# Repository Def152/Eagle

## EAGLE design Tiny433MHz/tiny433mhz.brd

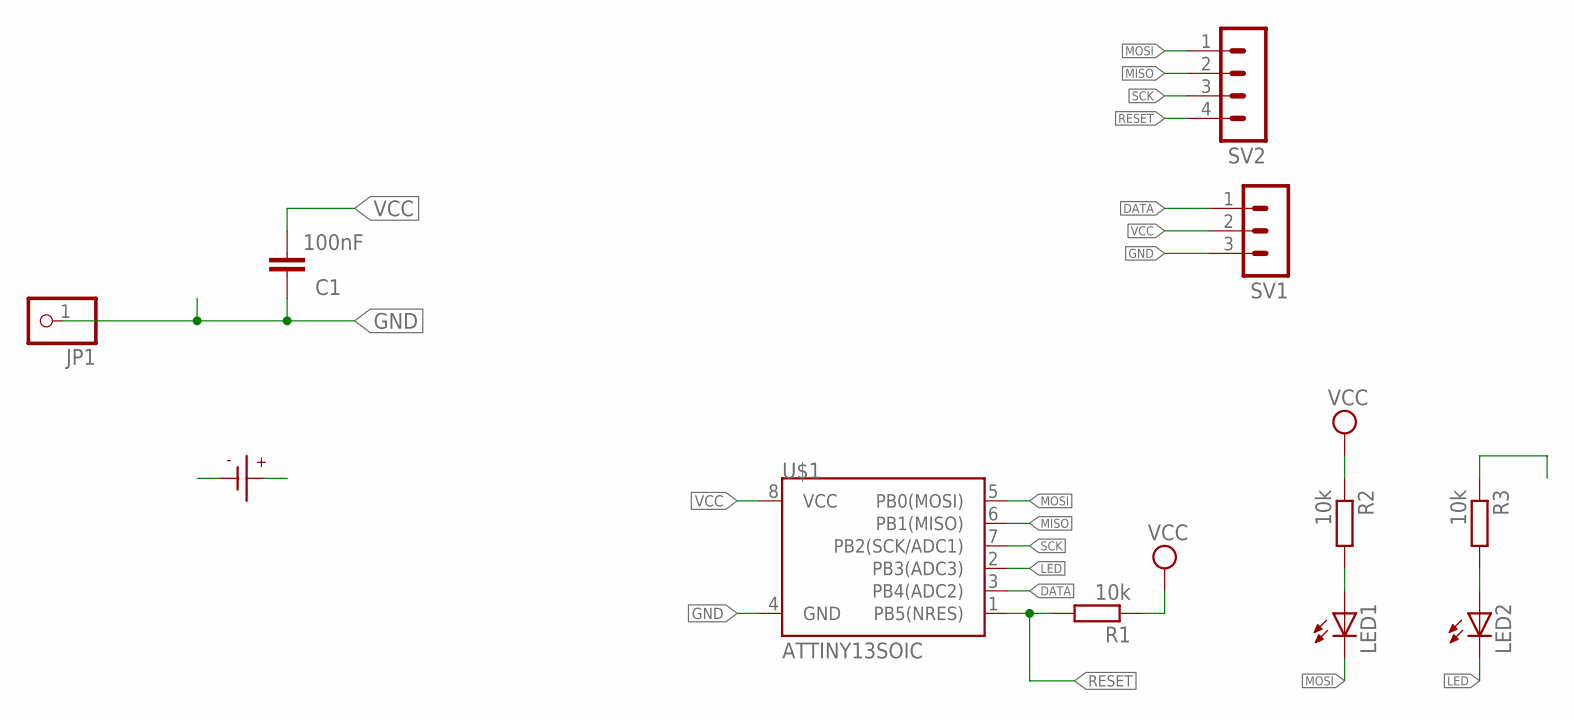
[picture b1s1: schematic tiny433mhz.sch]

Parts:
C1: 100nF; C0805
JP1: PINHD-1X1; 1X01
LED1, LED2: LEDCHIP-LED0805; CHIP-LED0805
R1, R2, R3: 10k; R0805
SV1: MA03-1
SV2: MA04-1
U$1: ATTINY13SOIC; SO08
U$3: CR2032; CR2032-THT

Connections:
DATA: SV1.1, U$1.3 (PB4(ADC2))
GND: C1.1, JP1.1, R3.1, SV1.3, U$1.4 (GND), U$3.-
LED: LED2.C, U$1.2 (PB3(ADC3))
MISO: SV2.2, U$1.6 (PB1(MISO))
MOSI: LED1.C, SV2.1, U$1.5 (PB0(MOSI))
unnamed: LED2.A, R3.2
unnamed: LED1.A, R2.2
RESET: R1.2, SV2.4, U$1.1 (PB5(NRES))
SCK: SV2.3, U$1.7 (PB2(SCK/ADC1))
VCC: C1.2, R1.1, R2.1, SV1.2, U$1.8 (VCC), U$3.+

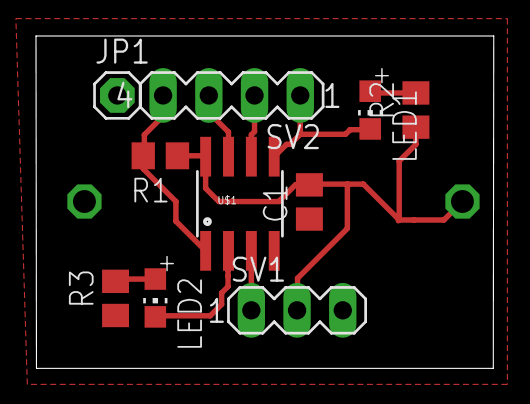
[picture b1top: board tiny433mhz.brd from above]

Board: 2 copper layers, 25.4 x 18.5 mm, 11 parts (1 on the bottom side), 10 nets.

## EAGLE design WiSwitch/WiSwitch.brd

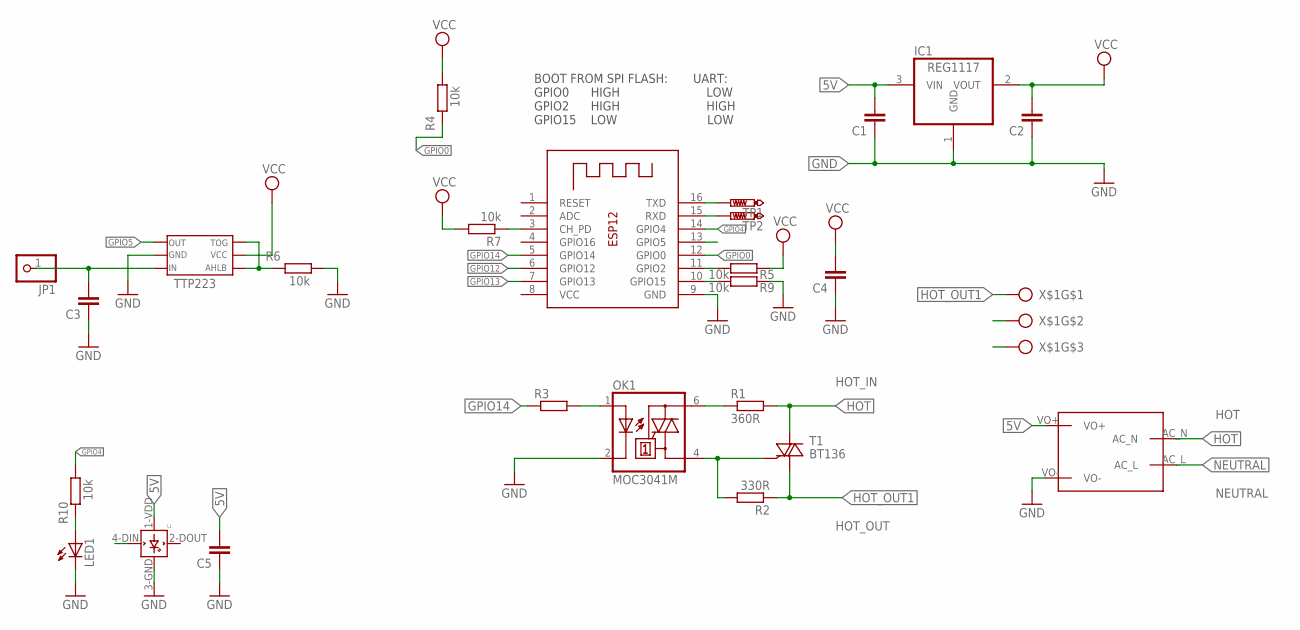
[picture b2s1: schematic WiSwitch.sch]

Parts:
C1, C2, C3, C4, C5: C-EUC0805; C0805
IC1: REG1117; SOT223
JP1: PINHD-1X1; 1X01
L1: WS2812B
LED1: LEDCHIP-LED0805; CHIP-LED0805
OK1: MOC3041M; DIL06
R1: 360R; 0207/10
R2: 330R; 0207/10
R3: R-EU_R0805; R0805
R4, R5, R6, R9, R10: 10k; R0805
R7: 10k; R0603
T1: BT136; TO220AB
TP1, TP2: PTR1B1,27; B1,27
U$2: MAINS_CONVERTERS; HLK-PM01
U$3: TTP223-BA6; SOT-23-6L
X1: ESP-12
X$1: ARK3

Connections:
5V: C1.2, C5.2, IC1.3 (VIN), L1.1-VDD (VDD), U$2.VO+
GND: C1.1, C2.1, C3.1, C4.1, C5.1, IC1.1 (GND), L1.3-GND (GND), LED1.C, OK1.2 (C), R6.2, R9.2, U$2.VO-, U$3.GND, X1.9 (GND)
GPIO0: R4.1, X1.12 (GPIO0)
GPIO4: R10.2, X1.14 (GPIO4)
GPIO5: U$3.OUT, X1.13 (GPIO5)
GPIO12: X1.6 (GPIO12)
GPIO13: L1.4-DIN (DIN), X1.7 (GPIO13)
GPIO14: R3.1, X1.5 (GPIO14)
HOT: R1.2, T1.2 (A2), U$2.AC_N, X$1.2
HOT_OUT1: R2.1, T1.1 (A1), X$1.1
IN: C3.2, JP1.1, U$3.IN
unnamed: OK1.1 (A), R3.2
unnamed: OK1.6 (A2), R1.1
unnamed: OK1.4 (A1), R2.2, T1.3 (G)
unnamed: R7.1, X1.3 (CH_PD)
unnamed: R6.1, U$3.AHLB, U$3.TOG
unnamed: LED1.A, R10.1
unnamed: R5.1, X1.11 (GPIO2)
unnamed: R9.1, X1.10 (GPIO15)
NEUTRAL: U$2.AC_L, X$1.3
RX: TP2.TP, X1.15 (RXD)
TX: TP1.TP, X1.16 (TXD)
VCC: C2.2, C4.2, IC1.2 (VOUT), R4.2, R5.2, R7.2, U$3.VCC, X1.8 (VCC)

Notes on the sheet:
HOT
NEUTRAL
HOT_IN
HOT_OUT
BOOT FROM SPI FLASH: UART: GPIO0 HIGH LOW GPIO2 HIGH HIGH GPIO15 LOW LOW

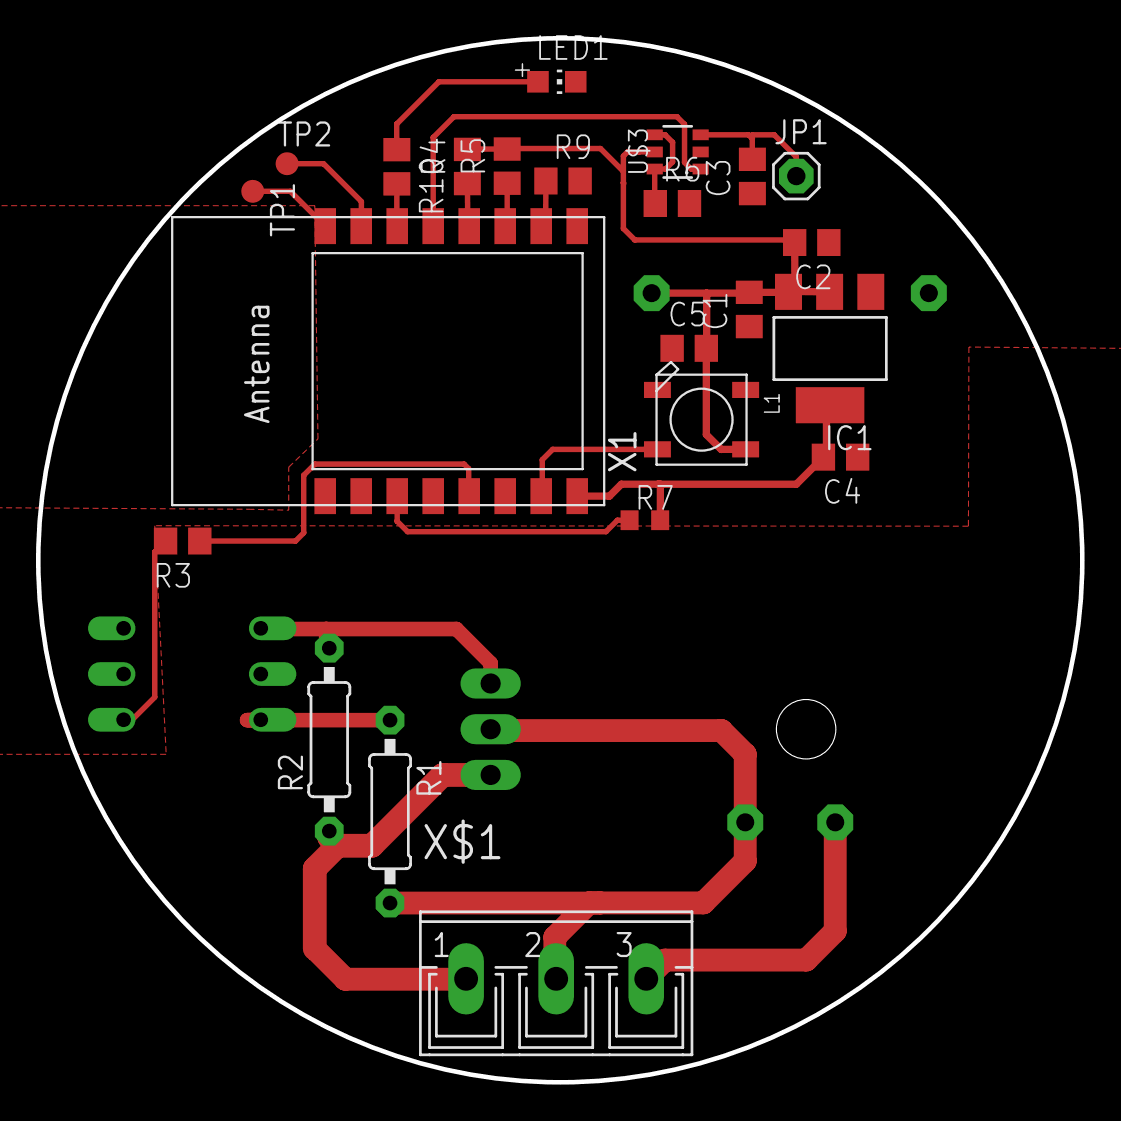
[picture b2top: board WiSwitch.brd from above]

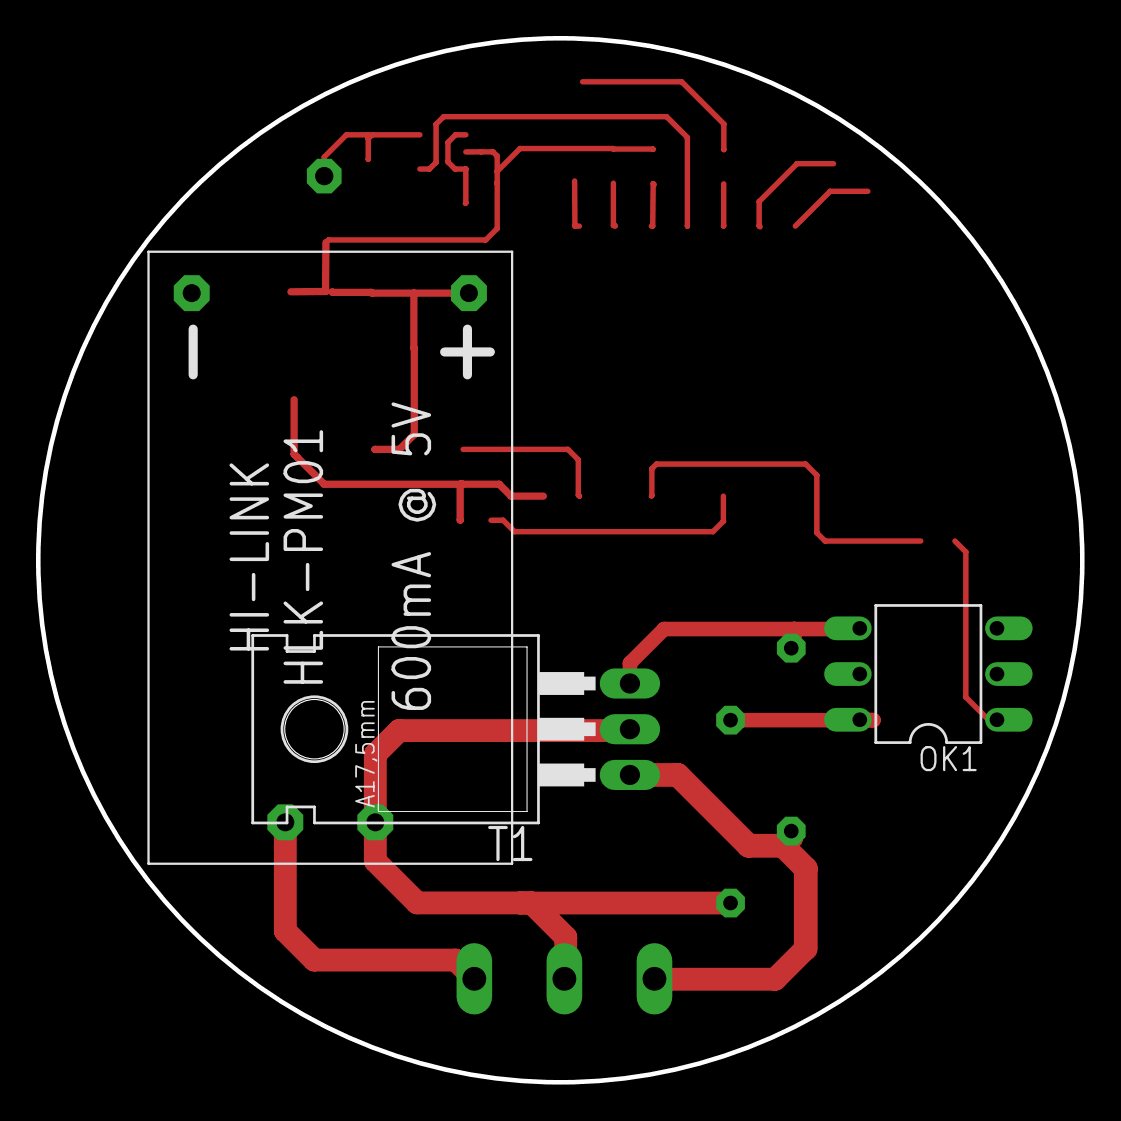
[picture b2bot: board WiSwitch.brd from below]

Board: 2 copper layers, 58.0 x 58.0 mm, 26 parts (3 on the bottom side), 22 nets.

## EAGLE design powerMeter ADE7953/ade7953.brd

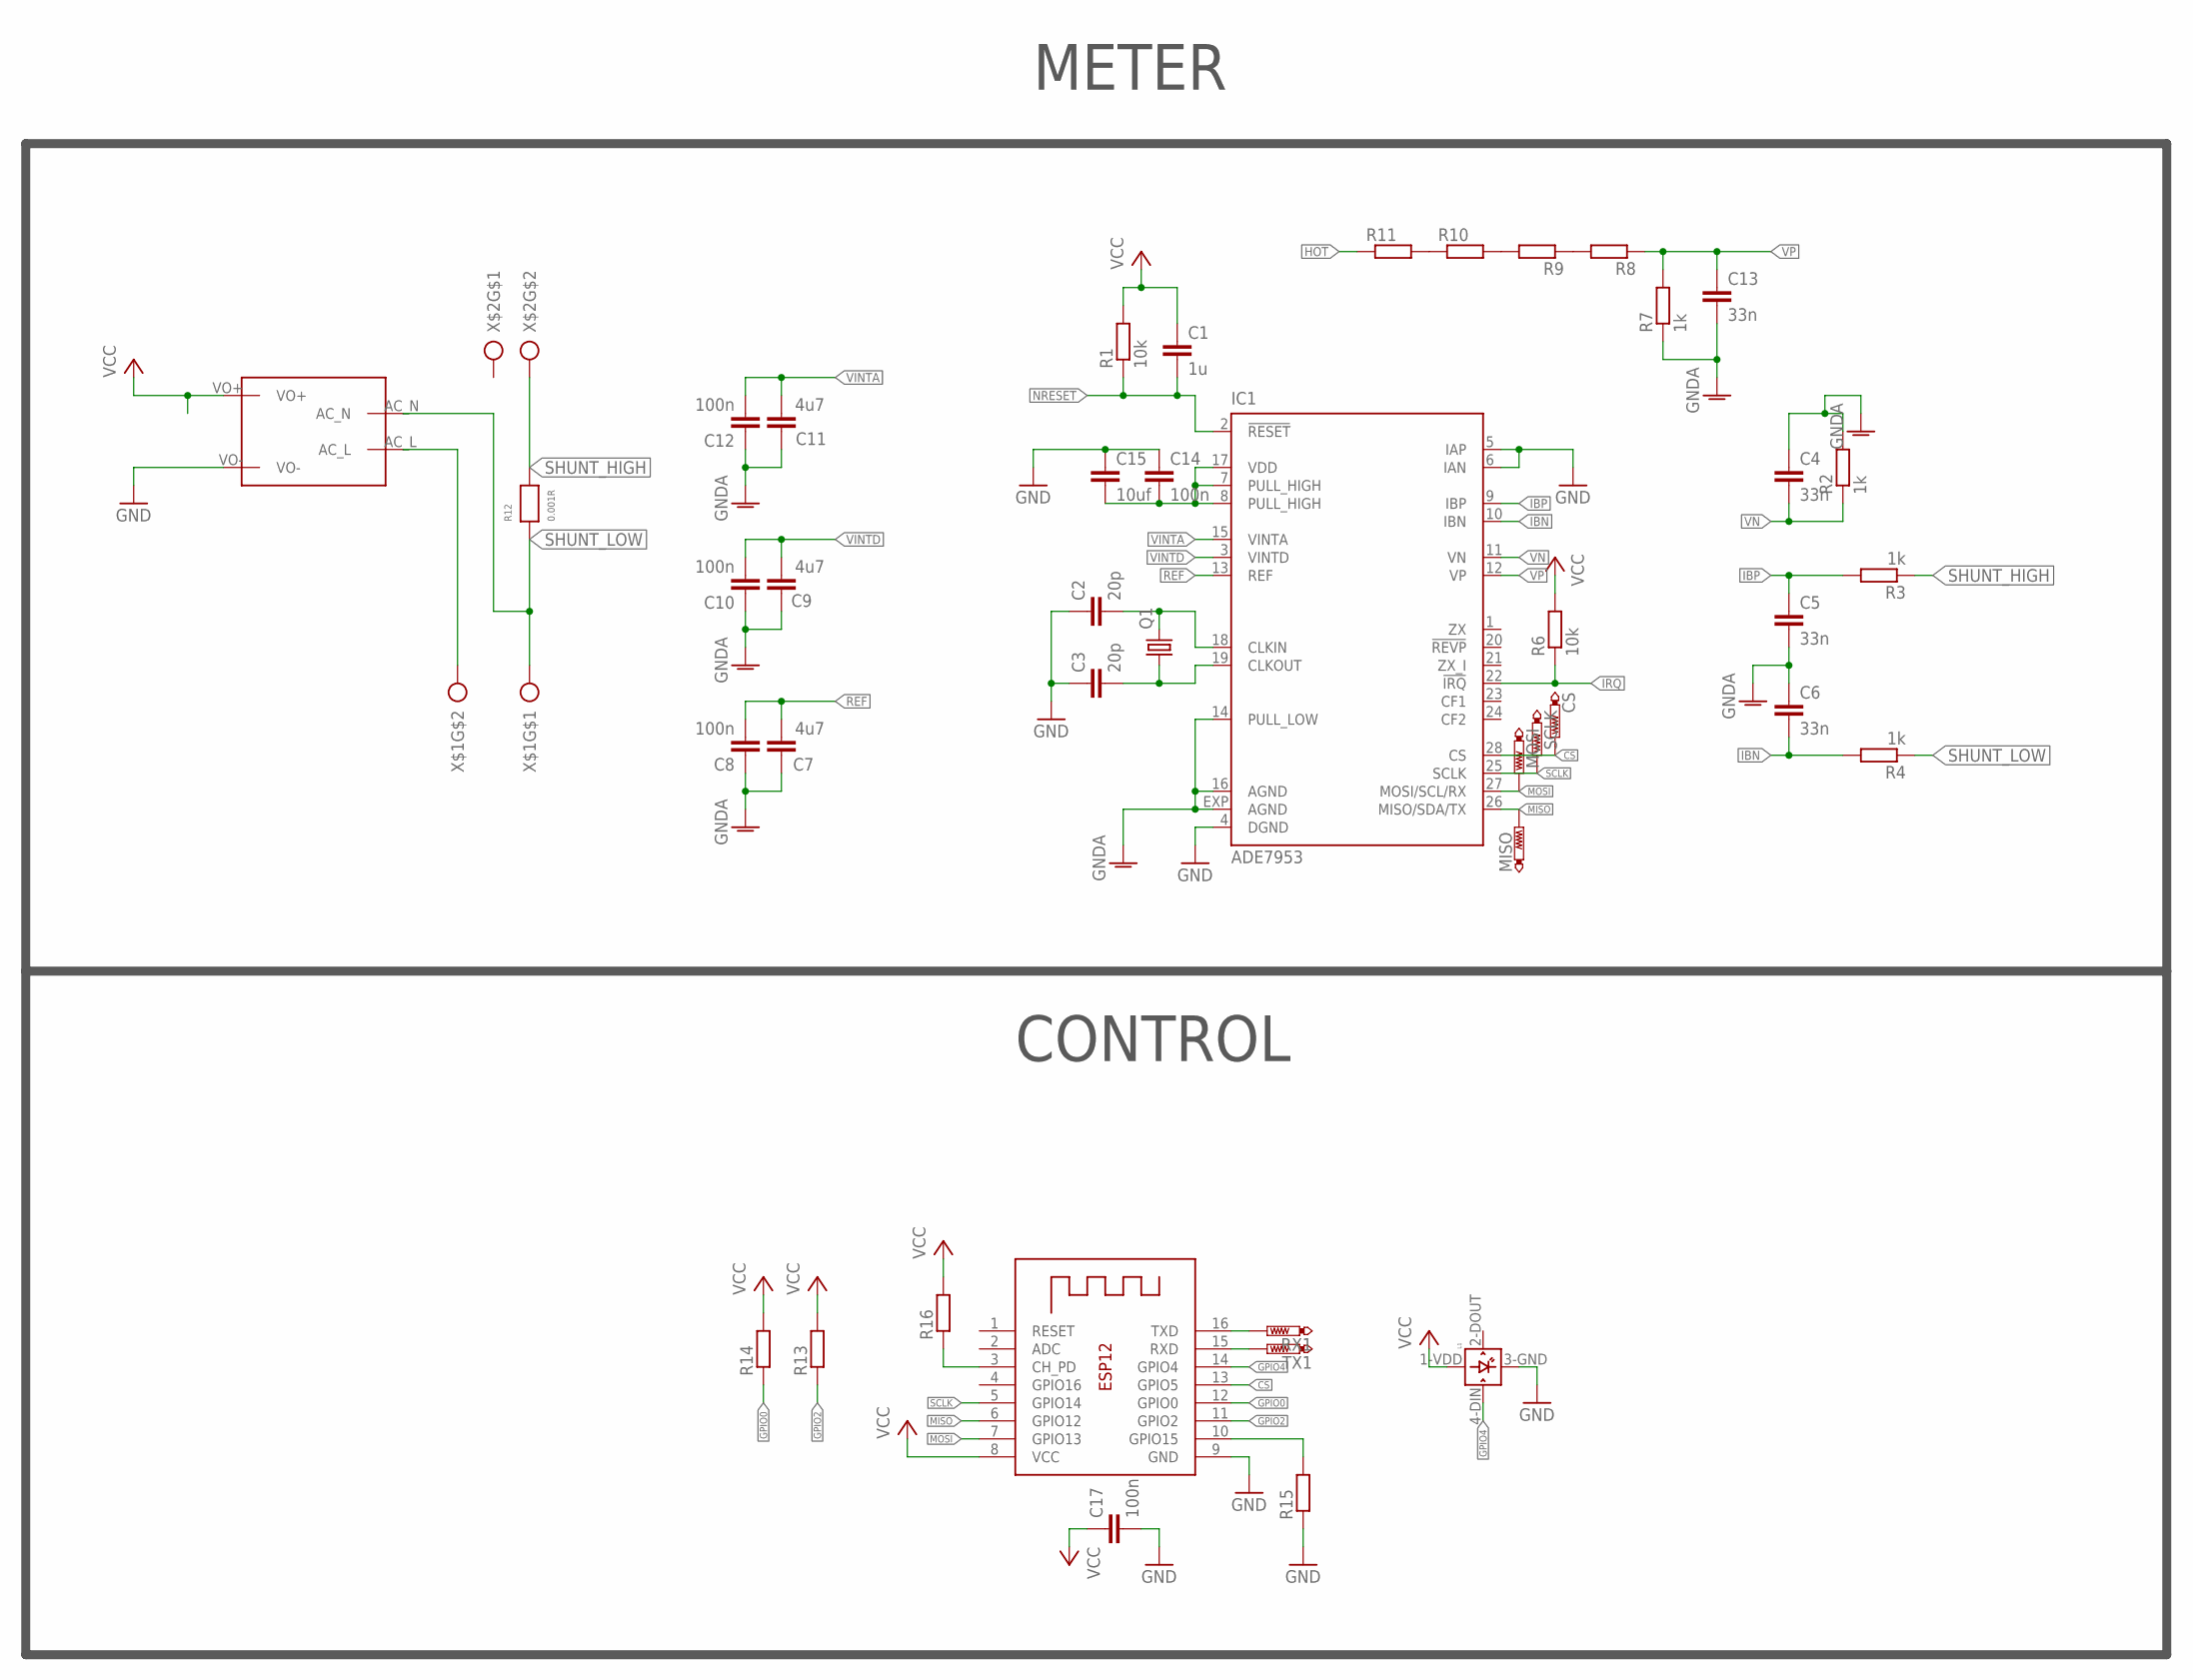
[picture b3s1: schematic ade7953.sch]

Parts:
C1: 1u; C0805
C2, C3: 20p; C0805
C4, C5, C6, C13: 33n; C0805
C7, C9, C11: 4u7; C0805
C8, C10, C12, C14, C17: 100n; C0805
C15: 10uf; C0805
CS: PTR1B1,27; B1,27
IC1: ADE7953; QFN28-ML
L1: WS2812B
MISO: PTR1B1,27; B1,27
MOSI: PTR1B1,27; B1,27
Q1: CRYSTALHC49UP; HC49UP
R1, R6: 10k; R0805
R2, R3, R4, R7: 1k; R0805
R8, R9: R-EU_R0805; R0805
R10, R11: R-EU_R1206; R1206
R12: 0.001R; WRS-2_4527
R13, R14, R15, R16: R-EU_R0603; R0603
RX1: PTR1B1,27; B1,27
SCLK: PTR1B1,27; B1,27
TX1: PTR1B1,27; B1,27
U$1: MAINS_CONVERTERS; HLK-PM01
X3: ESP-12
X$1, X$2: ARK2

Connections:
CLKIN: C2.2, IC1.18 (CLKIN), Q1.2
CLKOUT: C3.2, IC1.19 (CLKOUT), Q1.1
CS: CS.TP, IC1.28 (CS), X3.13 (GPIO5)
GND: C2.1, C3.1, C14.1, C15.1, C17.2, IC1.4 (DGND), IC1.5 (IAP), IC1.6 (IAN), L1.3-GND (GND), R15.1, U$1.VO-, X3.9 (GND)
GNDA: C4.1, C5.2, C6.1, C7.1, C8.1, C9.1, C10.1, C11.1, C12.1, C13.2, IC1.14 (PULL_LOW), IC1.16 (AGND), IC1.EXP (AGND), R2.2, R7.1
GPIO0: R14.1, X3.12 (GPIO0)
GPIO2: R13.1, X3.11 (GPIO2)
GPIO4: L1.4-DIN (DIN), X3.14 (GPIO4)
GPIO15: R15.2, X3.10 (GPIO15)
HOT: R11.1, U$1.AC_L, X$1.2
IBN: C6.2, IC1.10 (IBN), R4.2
IBP: C5.1, IC1.9 (IBP), R3.2
IRQ: IC1.22 (!IRQ!), R6.1
MISO: IC1.26 (MISO/SDA/TX), MISO.TP, X3.6 (GPIO12)
MOSI: IC1.27 (MOSI/SCL/RX), MOSI.TP, X3.7 (GPIO13)
unnamed: R9.2, R10.2
unnamed: R10.1, R11.2
unnamed: R16.1, X3.3 (CH_PD)
unnamed: R8.2, R9.1
NRESET: C1.2, IC1.2 (!RESET!), R1.1
REF: C7.2, C8.2, IC1.13 (REF)
RX: TX1.TP, X3.15 (RXD)
SCLK: IC1.25 (SCLK), SCLK.TP, X3.5 (GPIO14)
SHUNT_HIGH: R3.1, R12.2, X$2.2
SHUNT_LOW: R4.1, R12.1, U$1.AC_N, X$1.1
TX: RX1.TP, X3.16 (TXD)
VCC: C1.1, C14.2, C15.2, C17.1, IC1.7 (PULL_HIGH), IC1.8 (PULL_HIGH), IC1.17 (VDD), L1.1-VDD (VDD), R1.2, R6.2, R13.2, R14.2, R16.2, U$1.VO+, X3.8 (VCC)
VINTA: C11.2, C12.2, IC1.15 (VINTA)
VINTD: C9.2, C10.2, IC1.3 (VINTD)
VN: C4.2, IC1.11 (VN), R2.1
VP: C13.1, IC1.12 (VP), R7.2, R8.1

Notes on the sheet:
METER
CONTROL

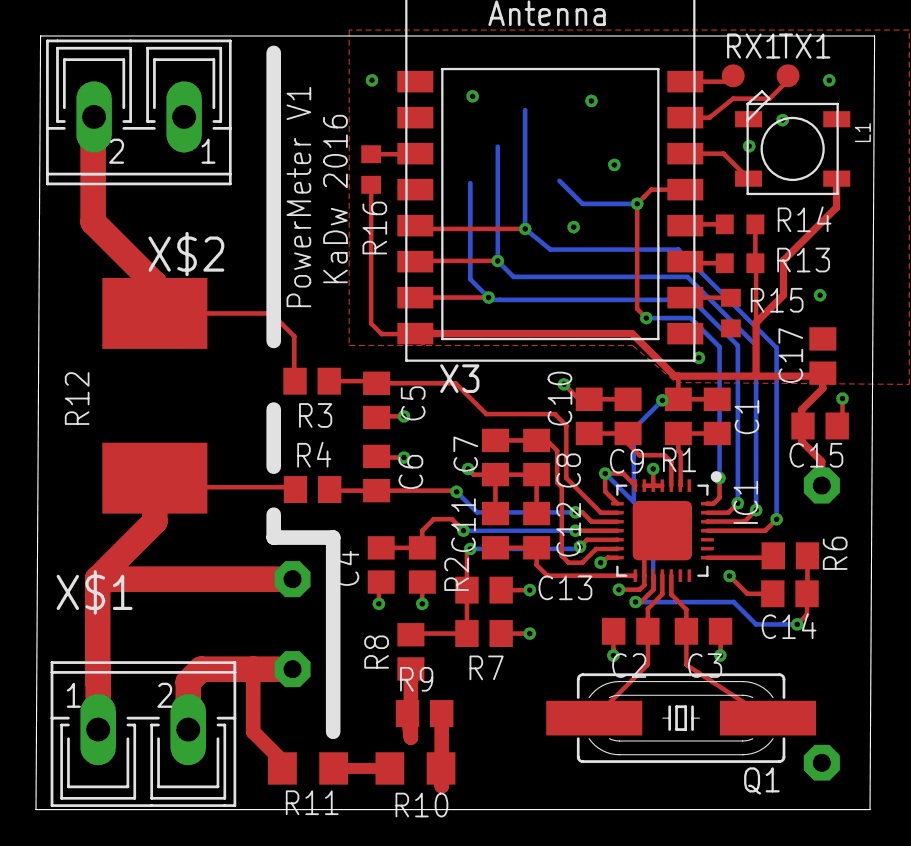
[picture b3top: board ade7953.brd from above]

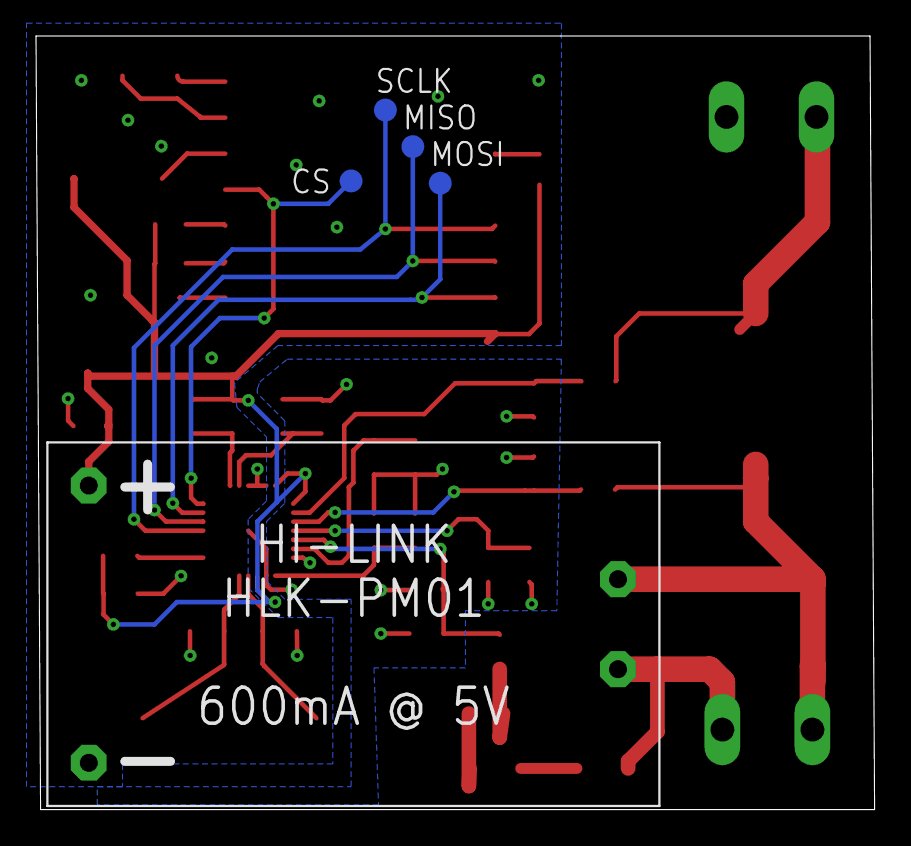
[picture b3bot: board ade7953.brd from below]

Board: 2 copper layers, 46.6 x 43.0 mm, 44 parts (5 on the bottom side), 31 nets.

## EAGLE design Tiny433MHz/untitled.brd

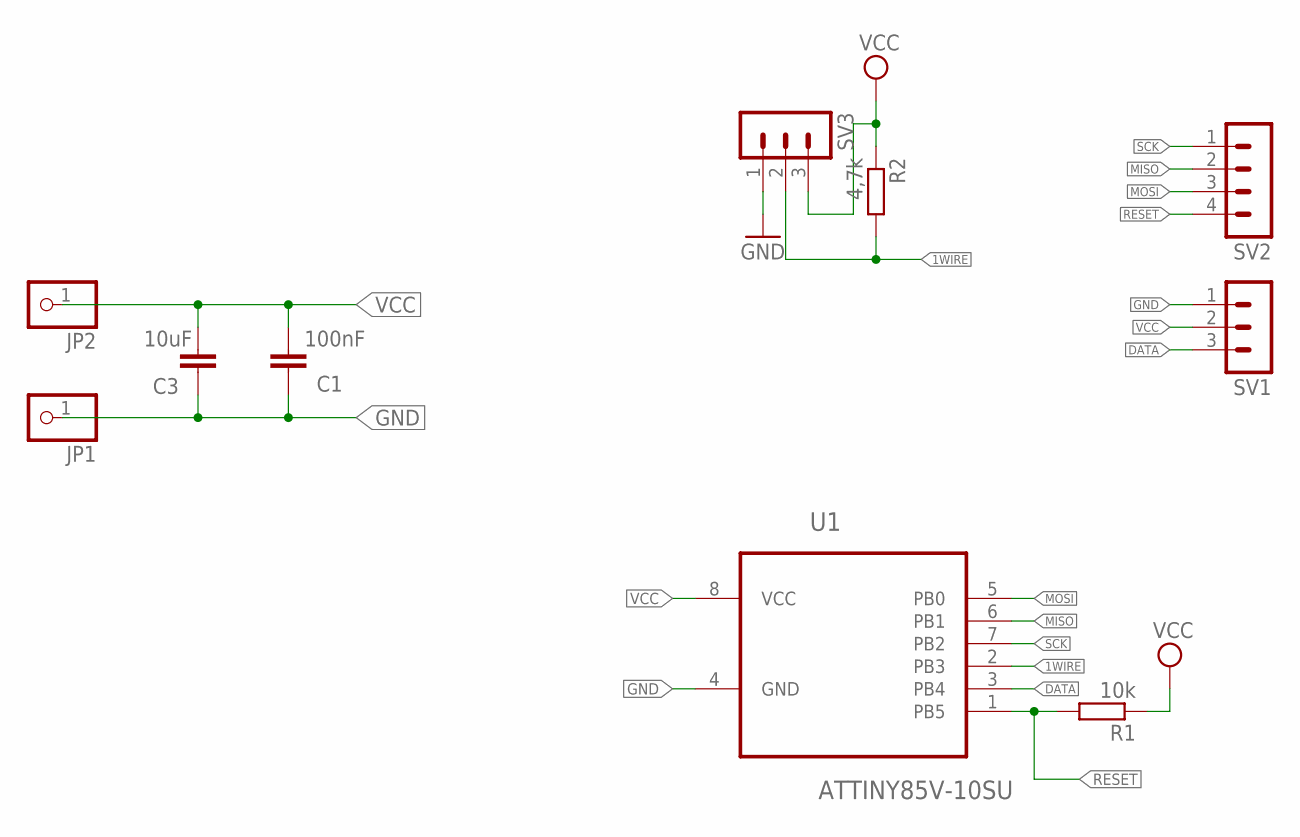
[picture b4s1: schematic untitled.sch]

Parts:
C1: 100nF; C0805
C3: 10uF; C1206
JP1, JP2: PINHD-1X1; 1X01
R1: 10k; R0805
R2: 4,7k; R0805
SV1, SV3: MA03-1
SV2: MA04-1
U1: ATTINY85V-10SU; SOIC127P798X216-8N

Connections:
1WIRE: R2.2, SV3.2, U1.2 (PB3)
DATA: SV1.3, U1.3 (PB4)
GND: C1.1, C3.2, JP1.1, SV1.1, SV3.1, U1.4 (GND)
MISO: SV2.2, U1.6 (PB1)
MOSI: SV2.3, U1.5 (PB0)
RESET: R1.2, SV2.4, U1.1 (PB5)
SCK: SV2.1, U1.7 (PB2)
VCC: C1.2, C3.1, JP2.1, R1.1, R2.1, SV1.2, SV3.3, U1.8 (VCC)

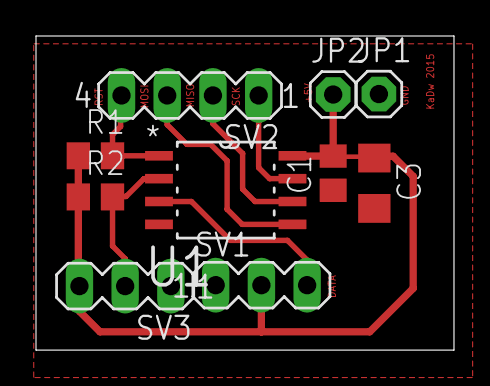
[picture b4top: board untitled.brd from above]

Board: 2 copper layers, 23.2 x 17.5 mm, 10 parts (0 on the bottom side), 8 nets.

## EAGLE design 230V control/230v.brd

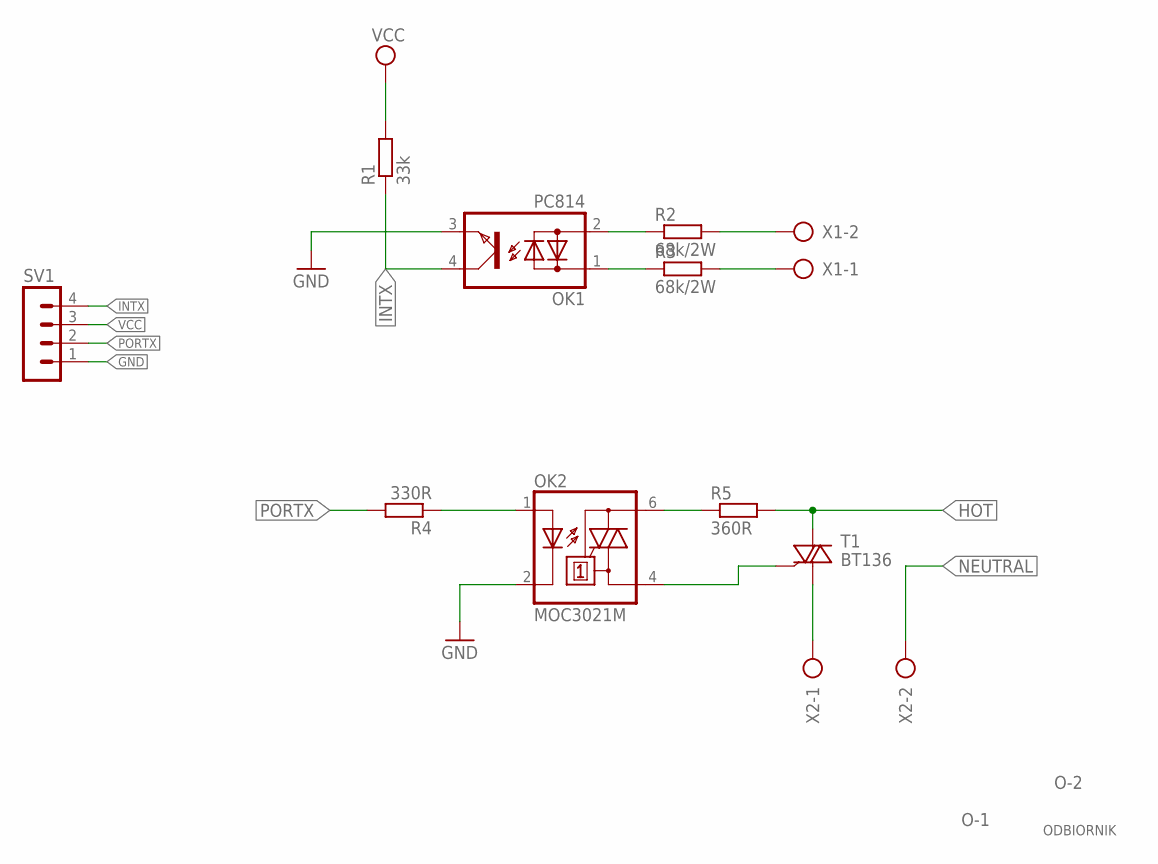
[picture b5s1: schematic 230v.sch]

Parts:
OK1: PC814; DIL04
OK2: MOC3021M; DIL06
R1: 33k; R0805
R2, R3: 68k/2W; 0309/12
R4: 330R; R0805
R5: 360R; 0207/7
SV1: MA04-1
T1: BT136; TO220AB
X1, X2: AK300/2

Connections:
GND: OK1.3 (E), OK2.2 (C), SV1.1
HOT: R2.2, R5.2, T1.2 (A2), X1.2
INTX: OK1.4 (C), R1.1, SV1.4
unnamed: OK1.1 (AC1), R3.1
unnamed: OK1.2 (AC2), R2.1
unnamed: OK2.6 (A2), R5.1
unnamed: OK2.1 (A), R4.1
unnamed: T1.1 (A1), X2.1
unnamed: OK2.4 (A1), T1.3 (G)
NEUTRAL: R3.2, X1.1, X2.2
PORTX: R4.2, SV1.2
VCC: R1.2, SV1.3

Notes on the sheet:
O-1
O-2
ODBIORNIK

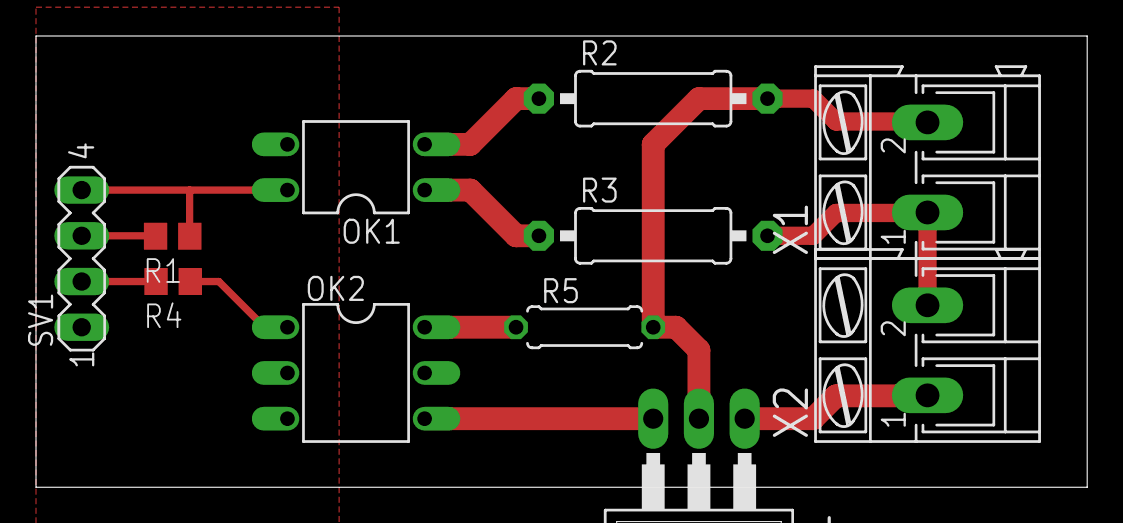
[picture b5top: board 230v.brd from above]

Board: 2 copper layers, 58.4 x 25.1 mm, 11 parts (0 on the bottom side), 12 nets.

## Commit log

2016-08-20 updated WiSwitch, tiny433mhz and ade7953

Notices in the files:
parts and their libraries:
SparkFun: Licensing: CC v3.0 Share-Alike You are welcome to use this library for commercial purposes.
